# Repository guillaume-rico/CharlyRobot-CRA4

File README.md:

# CharlyRobot-CRA4

# Carte de puissance

Analyse de la carte de puissance :

ALIM 1 :

 * Tension sortie transformateur : 23.6VAC
 * Tension sortie : 31VDC

ALIM 2 :

 * Tension sortie transformateur : 21VAC
 * Tension sortie : 28VDC

[Schématique](/carte_puissance/carte_puissance_schematique.pdf)

[PCB](/carte_puissance/carte_puissance_PCB.pdf)

# Indicateurs lumineux

Tension d'alimentation : 12VDC -> 32VDC
Courant : 
 * 6mA pour 12VDC
 * 20mA pour 30VDC

| Témoin | Couleur fil |
| ------------- | ------------- |
| Masse commune | Noir |
| Alimentation électrique | Rouge |
| Alarme | Jaune / Noir |
| STOP | Bleu / Gris |
| Broche / Spindle | Violet |
| Capteur Outil | Orange / Noir |
| X Ok | Marron |
| Y Ok | Vert |
| Z Ok | Bleu |

# Carte de commande

La position des capteurs fin de course (1 seul par axe) :

## Drivers commande moteur pas à pas 

C'est des drivers TB6600.
4 microstep (donc 800 steps par tour).
3A pour X et Y , 2A pour Z

Positionnement des switch :

| Switch | Valeur |
| ------------- | ------------- |
| S1 | ON |
| S2 | OFF |
| S3 | OFF |
| S4 | Z : ON |
| S5 | Y et Y : ON |
| S6 | OFF |

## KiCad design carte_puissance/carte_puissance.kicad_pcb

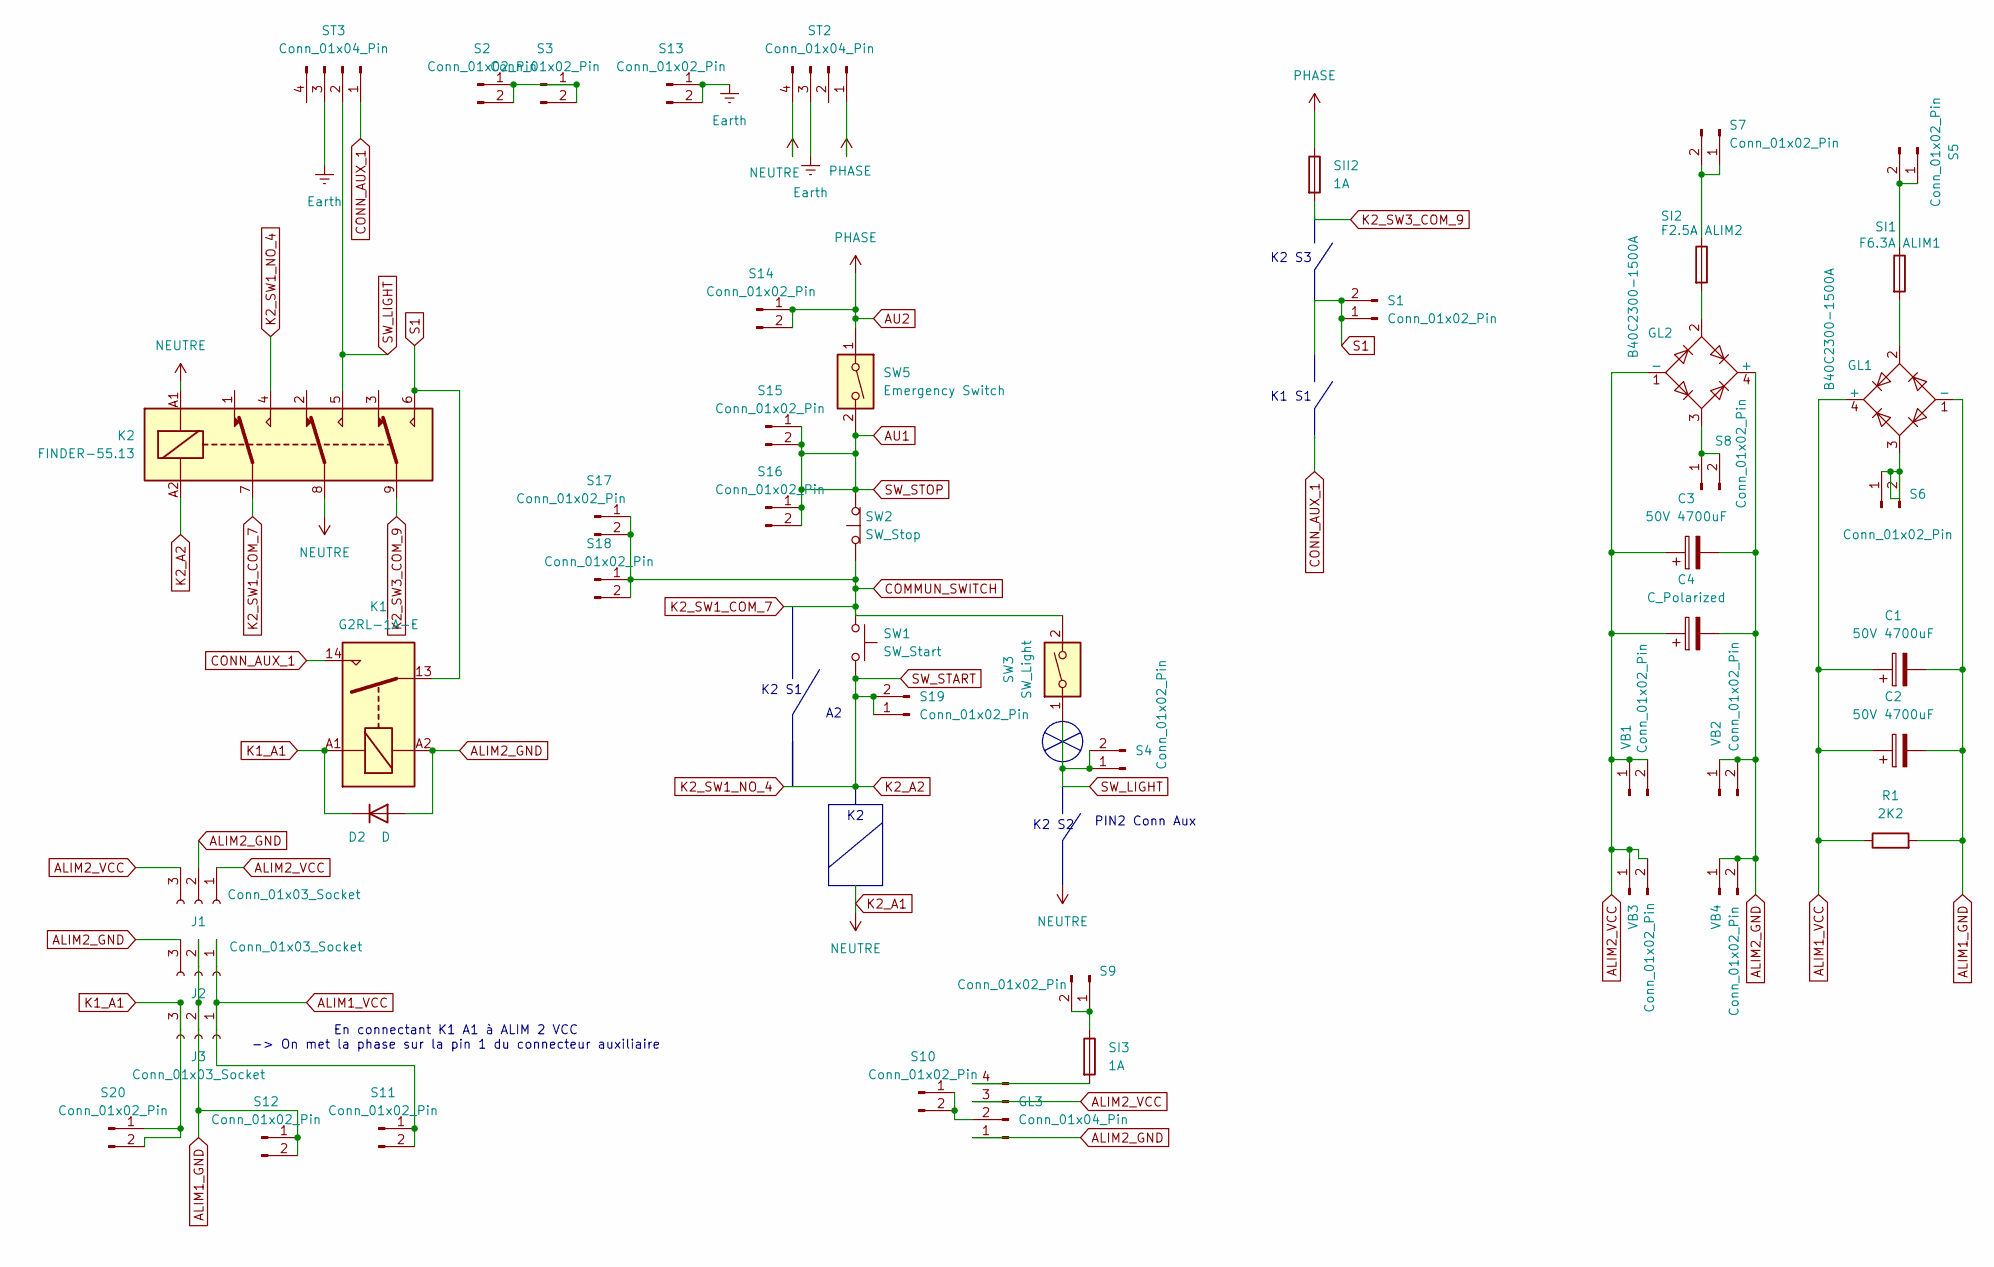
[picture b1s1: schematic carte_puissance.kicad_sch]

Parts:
C1, C3: 50V 4700uF; CP_Radial_D25.0mm_P10.00mm_SnapIn
C2: 50V 4700uF; CP_Radial_D30.0mm_P10.00mm_SnapIn
C4: C_Polarized; CP_Radial_D25.0mm_P10.00mm_SnapIn
D2: D; D_5W_P10.16mm_Horizontal
GL1, GL2: B40C2300-1500A; Diode_Bridge_19.0x3.5x10.0mm_P5.0mm
GL3: Conn_01x04_Pin; PhoenixContact_MSTBVA_2,5_4-G_1x04_P5.00mm_Vertical
J1, J2, J3: Conn_01x03_Socket; SolderWire-1sqmm_1x03_P7.8mm_D1.4mm_OD3.9mm
K1: G2RL-1A-E; Relay_SPST_Omron_G2RL-1A-E
K2: FINDER-55.13; Relay_SPDT_Finder_40.61
R1: 2K2; R_Axial_Power_L25.0mm_W6.4mm_P30.48mm
S1, S2, S3, S4, S5, S6, S7, S8, S9, S10, S11, S12, S13, S14, S15, S16, S17, S18, S19, S20: Conn_01x02_Pin; SolderWire-0.5sqmm_1x02_P4.6mm_D0.9mm_OD2.1mm
SI1: F6.3A ALIM1; Fuseholder_Clip-5x20mm_Keystone_3512P_Inline_P23.62x7.27mm_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
SI2: F2.5A ALIM2; Fuseholder_Clip-5x20mm_Keystone_3512P_Inline_P23.62x7.27mm_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
SI3: 1A; Fuseholder_Clip-5x20mm_Keystone_3512P_Inline_P23.62x7.27mm_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
SII2: 1A; Fuseholder_Cylinder-5x20mm_EATON_HBW_Vertical_Closed
ST2, ST3: Conn_01x04_Pin; PhoenixContact_MSTBVA_2,5_4-G_1x04_P5.00mm_Vertical
SW1: SW_Start
SW2: SW_Stop
SW3: SW_Light
SW5: Emergency Switch
VB1, VB2, VB3, VB4: Conn_01x02_Pin; SolderWire-0.5sqmm_1x02_P4.6mm_D0.9mm_OD2.1mm

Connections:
ALIM1_GND: C1.2, C2.2, GL1.1 (-), J2.2, J3.2, R1.2, S12.1, S12.2
ALIM1_VCC: C1.1, C2.1, GL1.4 (+), J2.1, J3.1, R1.1, S11.1, S11.2
ALIM2_GND: C3.2, C4.2, D2.2 (A), GL2.4 (+), GL3.1, J1.2, J2.3, K1.A2, VB2.1, VB2.2, VB4.1, VB4.2
ALIM2_VCC: C3.1, C4.1, GL2.1 (-), GL3.3, J1.1, J1.3, VB1.1, VB1.2, VB3.1, VB3.2
AU1: S15.1, S15.2, S16.1, S16.2, SW2.2 (B), SW5.2
AU2: S14.1, S14.2, SII2.1, ST2.1, SW5.1
COMMUN_SWITCH: K2.7, S17.1, S17.2, S18.1, S18.2, SW1.1, SW2.1 (A), SW3.2
CONN_AUX_1: K1.14, ST3.1
Earth: S13.1, S13.2, ST2.3, ST3.3
K1_A1: D2.1 (K), J3.3, K1.A1, S20.1, S20.2
K2_A1: K2.8, K2.A1, ST2.4
K2_A2: K2.4, K2.A2, S19.1, S19.2, SW1.2
K2_SW3_COM_9: K2.9, SII2.2
unnamed: GL1.2, SI1.2
unnamed: GL2.2, SI2.2
unnamed: GL3.2, S10.1, S10.2
unnamed: GL3.4, SI3.2
unnamed: S2.1, S2.2, S3.1, S3.2
unnamed: S5.1, S5.2, SI1.1
unnamed: GL1.3, S6.1, S6.2
unnamed: S7.1, S7.2, SI2.1
unnamed: GL2.3, S8.1, S8.2
unnamed: S9.1, S9.2, SI3.1
S1: K1.13, K2.6, S1.1, S1.2
SW_LIGHT: K2.5, S4.1, S4.2, ST3.2, SW3.1

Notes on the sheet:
K2 S3
En connectant K1 A1 à ALIM 2 VCC -> On met la phase sur la pin 1 du connecteur auxiliaire
K2 S2
K2 S1
PIN2 Conn Aux
K1 S1

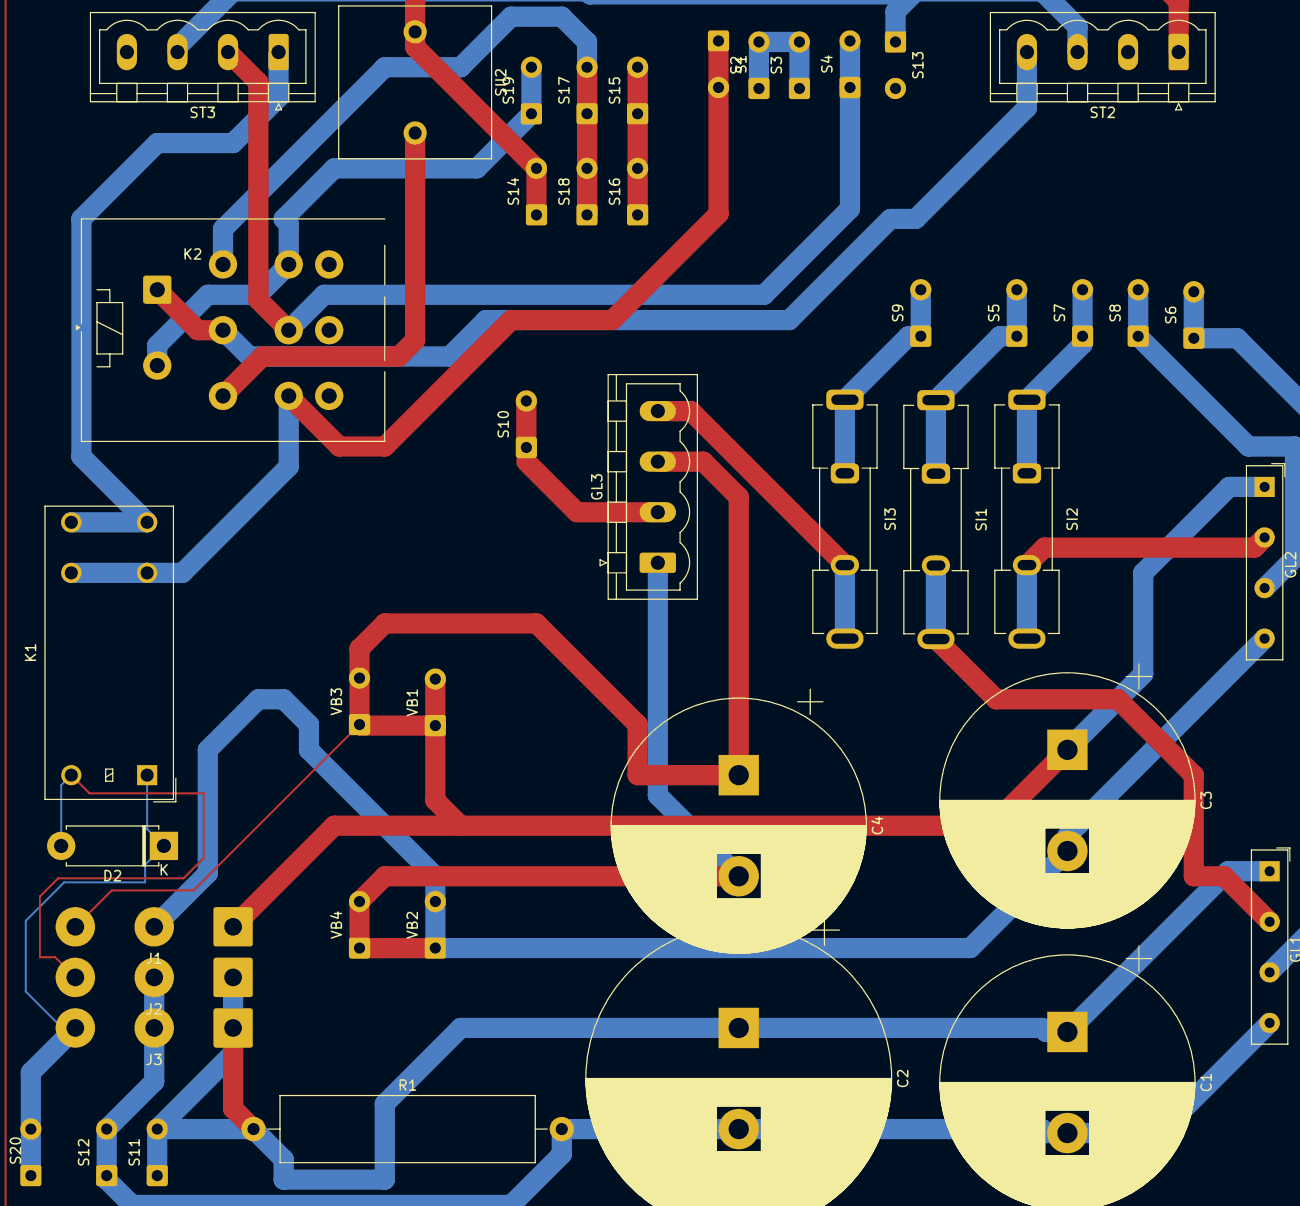
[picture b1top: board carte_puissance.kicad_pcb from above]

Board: 2 copper layers, 44 parts (0 on the bottom side), 25 nets.

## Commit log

2025-02-25 Creation
